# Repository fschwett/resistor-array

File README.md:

# Resistor array

## Idea:

I wanted to have a resistor array for test purposes. After seeing extremely expensive ones online I decided to create my own. My plan was to order it along with other PCBs, but that didn't end up happening.

## Concept:

An array of resistors which can be added to or removed from the total resistance. I wanted to order five PCBs to be able to play around with values more freely and be able to for example coordinate two resistances. I went with the classic 1, 2, 3, 4 design most of these arrays use. This means I have 1 Ω, 10 Ω, 100 Ω, 1 kΩ, 10 kΩ, 100 kΩ and 1 MΩ, then 2 Ω, 20 Ω and so on. This let's me get any nominal value from 0 Ω to 11.111.110 Ω.

## Implementation:

I had some SMD SPDT slide switches laying around. I chose SMD, because it would give the PCB a clean back. THT could've made contact with other parts and could've ended up shorting the whole thing. For some of the values I had to comine resistors, because I didn't have the right ones or they simple weren't part of the e series. I also used SMD resistors. This had the disadvantage of a low power rating though. Mine are .25 W 1% resistors. Unfortunately I don't know the temperature coefficient of these resistors, but I assume it's between 100 ppm and 200 ppm.

That's the actual design:

The traces are as large as possible to reduce resistance.

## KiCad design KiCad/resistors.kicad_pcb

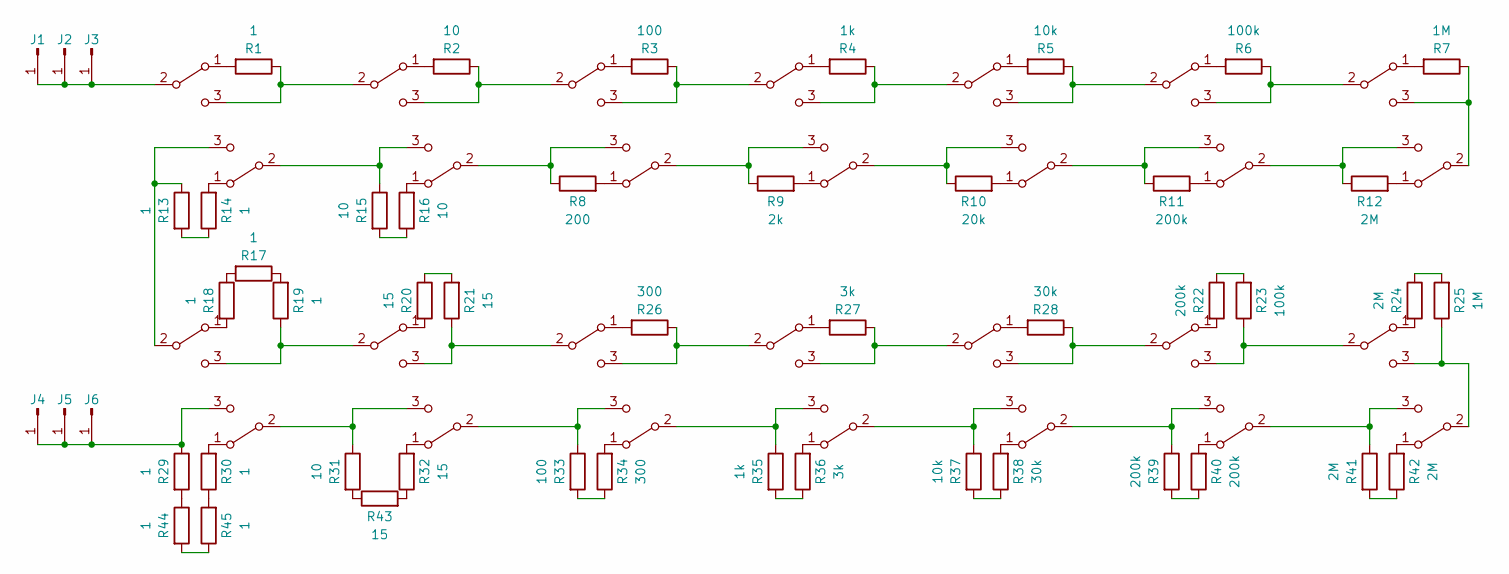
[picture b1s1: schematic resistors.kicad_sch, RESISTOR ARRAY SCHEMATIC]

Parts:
J1, J2, J3, J4, J5, J6: Conn_01x01_Pin; PinSocket_1x01_P2.54mm_Vertical
R1, R13, R14, R17, R18, R19, R29, R30, R44, R45: 1; R_1206_3216Metric_Pad1.30x1.75mm_HandSolder
R2, R15, R16, R31: 10; R_1206_3216Metric_Pad1.30x1.75mm_HandSolder
R3, R33: 100; R_1206_3216Metric_Pad1.30x1.75mm_HandSolder
R4, R35: 1k; R_1206_3216Metric_Pad1.30x1.75mm_HandSolder
R5, R37: 10k; R_1206_3216Metric_Pad1.30x1.75mm_HandSolder
R6, R23: 100k; R_1206_3216Metric_Pad1.30x1.75mm_HandSolder
R7, R25: 1M; R_1206_3216Metric_Pad1.30x1.75mm_HandSolder
R8: 200; R_1206_3216Metric_Pad1.30x1.75mm_HandSolder
R9: 2k; R_1206_3216Metric_Pad1.30x1.75mm_HandSolder
R10: 20k; R_1206_3216Metric_Pad1.30x1.75mm_HandSolder
R11, R22, R39, R40: 200k; R_1206_3216Metric_Pad1.30x1.75mm_HandSolder
R12, R24, R41, R42: 2M; R_1206_3216Metric_Pad1.30x1.75mm_HandSolder
R20, R21, R32, R43: 15; R_1206_3216Metric_Pad1.30x1.75mm_HandSolder
R26, R34: 300; R_1206_3216Metric_Pad1.30x1.75mm_HandSolder
R27, R36: 3k; R_1206_3216Metric_Pad1.30x1.75mm_HandSolder
R28, R38: 30k; R_1206_3216Metric_Pad1.30x1.75mm_HandSolder
SW1, SW2, SW3, SW4, SW5, SW6, SW7, SW8, SW9, SW10, SW11, SW12, SW13, SW14, SW15, SW16, SW17, SW18, SW19, SW20, SW21, SW22, SW23, SW24, SW25, SW26, SW27, SW28: SW_SPDT; SLW9135352ASMT

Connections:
unnamed: J1.1, J2.1, J3.1, SW1.2 (B)
unnamed: J4.1, J5.1, J6.1, R29.1, SW22.3 (C)
unnamed: R13.2, R14.1
unnamed: R15.2, R16.1
unnamed: R17.1, R19.2
unnamed: R17.2, R18.1
unnamed: R20.1, R21.2
unnamed: R22.1, R23.2
unnamed: R24.1, R25.2
unnamed: R29.2, R44.1
unnamed: R30.1, R45.2
unnamed: R31.2, R43.1
unnamed: R32.1, R43.2
unnamed: R33.2, R34.1
unnamed: R35.2, R36.1
unnamed: R37.2, R38.1
unnamed: R39.2, R40.1
unnamed: R41.2, R42.1
unnamed: R44.2, R45.1
unnamed: R1.2, SW1.1 (A)
unnamed: R1.1, SW1.3 (C), SW2.2 (B)
unnamed: R2.2, SW2.1 (A)
unnamed: R2.1, SW2.3 (C), SW3.2 (B)
unnamed: R3.2, SW3.1 (A)
unnamed: R3.1, SW3.3 (C), SW4.2 (B)
unnamed: R4.2, SW4.1 (A)
unnamed: R4.1, SW4.3 (C), SW5.2 (B)
unnamed: R5.2, SW5.1 (A)
unnamed: R5.1, SW5.3 (C), SW6.2 (B)
unnamed: R6.2, SW6.1 (A)
unnamed: R6.1, SW6.3 (C), SW7.2 (B)
unnamed: R7.2, SW7.1 (A)
unnamed: R14.2, SW8.1 (A)
unnamed: R15.1, SW8.2 (B), SW9.3 (C)
unnamed: R16.2, SW9.1 (A)
unnamed: R8.2, SW10.1 (A)
unnamed: R9.1, SW10.2 (B), SW11.3 (C)
unnamed: R8.1, SW9.2 (B), SW10.3 (C)
unnamed: R9.2, SW11.1 (A)
unnamed: R10.1, SW11.2 (B), SW12.3 (C)
unnamed: R10.2, SW12.1 (A)
unnamed: R11.1, SW12.2 (B), SW13.3 (C)
unnamed: R11.2, SW13.1 (A)
unnamed: R12.1, SW13.2 (B), SW14.3 (C)
unnamed: R12.2, SW14.1 (A)
unnamed: R7.1, SW7.3 (C), SW14.2 (B)
unnamed: R18.2, SW15.1 (A)
unnamed: R13.1, SW8.3 (C), SW15.2 (B)
unnamed: R19.1, SW15.3 (C), SW16.2 (B)
unnamed: R20.2, SW16.1 (A)
unnamed: R21.1, SW16.3 (C), SW17.2 (B)
unnamed: R26.2, SW17.1 (A)
unnamed: R26.1, SW17.3 (C), SW18.2 (B)
unnamed: R27.2, SW18.1 (A)
unnamed: R27.1, SW18.3 (C), SW19.2 (B)
unnamed: R28.2, SW19.1 (A)
unnamed: R28.1, SW19.3 (C), SW20.2 (B)
unnamed: R22.2, SW20.1 (A)
unnamed: R23.1, SW20.3 (C), SW21.2 (B)
unnamed: R24.2, SW21.1 (A)
unnamed: R25.1, SW21.3 (C), SW28.2 (B)
unnamed: R30.2, SW22.1 (A)
unnamed: R31.1, SW22.2 (B), SW23.3 (C)
unnamed: R32.2, SW23.1 (A)
unnamed: R33.1, SW23.2 (B), SW24.3 (C)
unnamed: R34.2, SW24.1 (A)
unnamed: R35.1, SW24.2 (B), SW25.3 (C)
unnamed: R36.2, SW25.1 (A)
unnamed: R37.1, SW25.2 (B), SW26.3 (C)
unnamed: R38.2, SW26.1 (A)
unnamed: R39.1, SW26.2 (B), SW27.3 (C)
unnamed: R40.2, SW27.1 (A)
unnamed: R41.1, SW27.2 (B), SW28.3 (C)
unnamed: R42.2, SW28.1 (A)

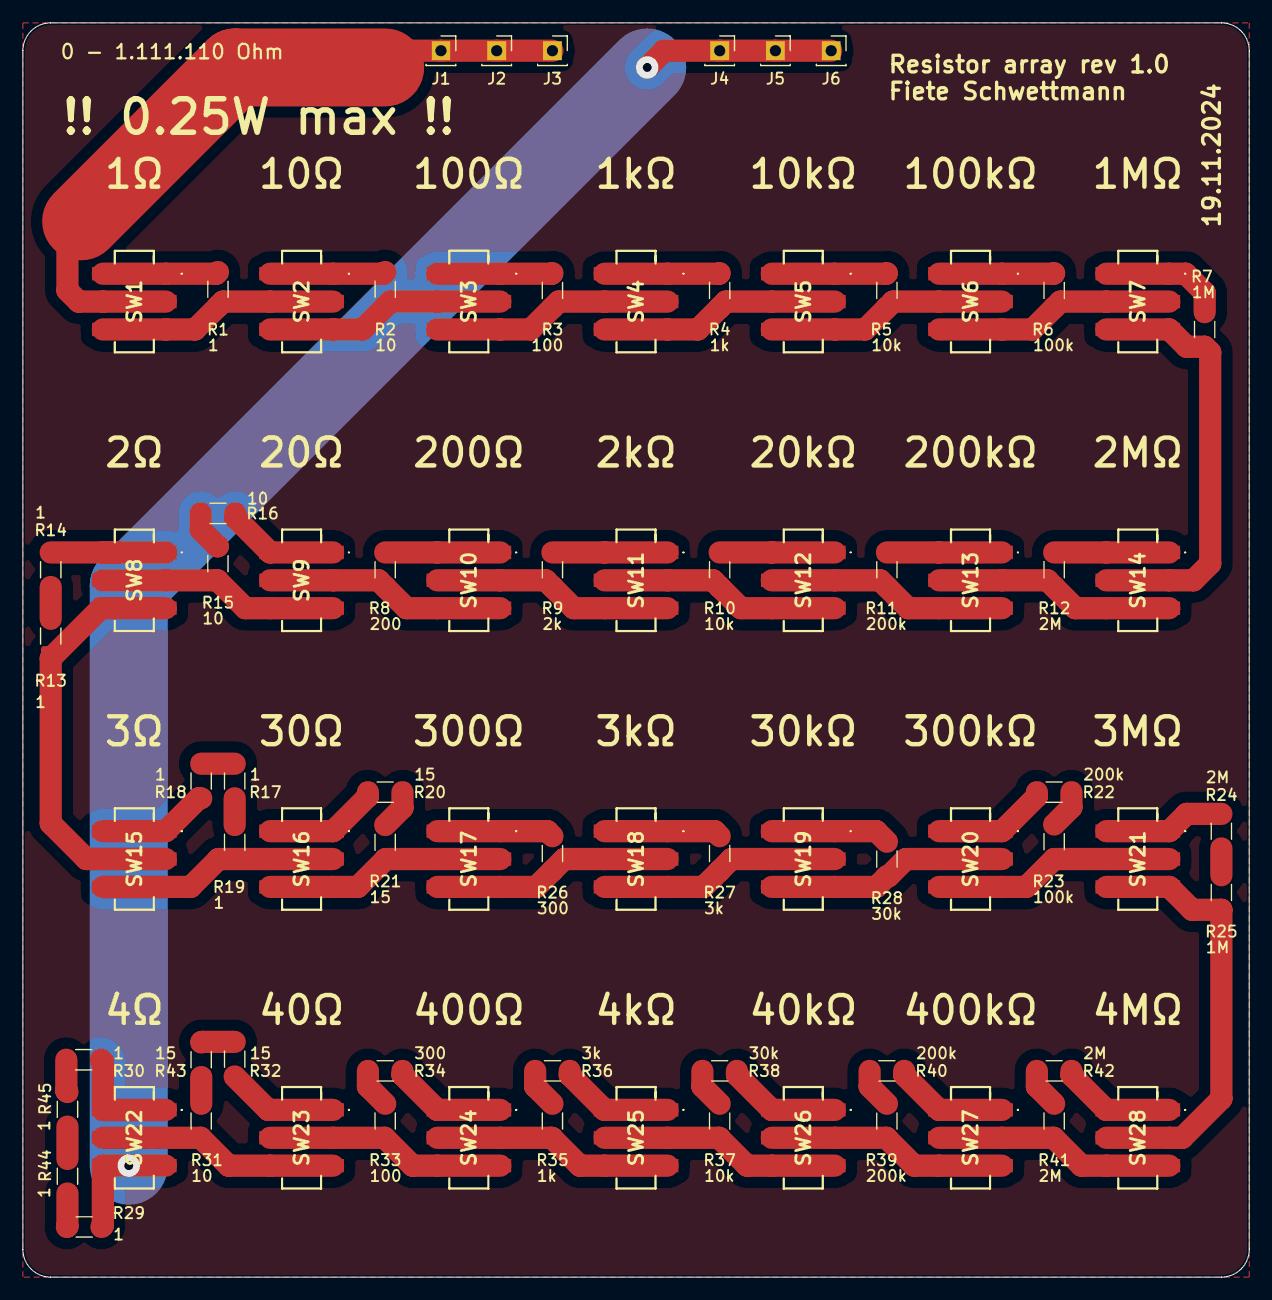
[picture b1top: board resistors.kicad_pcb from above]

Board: 2 copper layers, 110.0 x 112.5 mm, 79 parts (0 on the bottom side), 74 nets.

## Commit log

2026-05-28 restructured project directory
